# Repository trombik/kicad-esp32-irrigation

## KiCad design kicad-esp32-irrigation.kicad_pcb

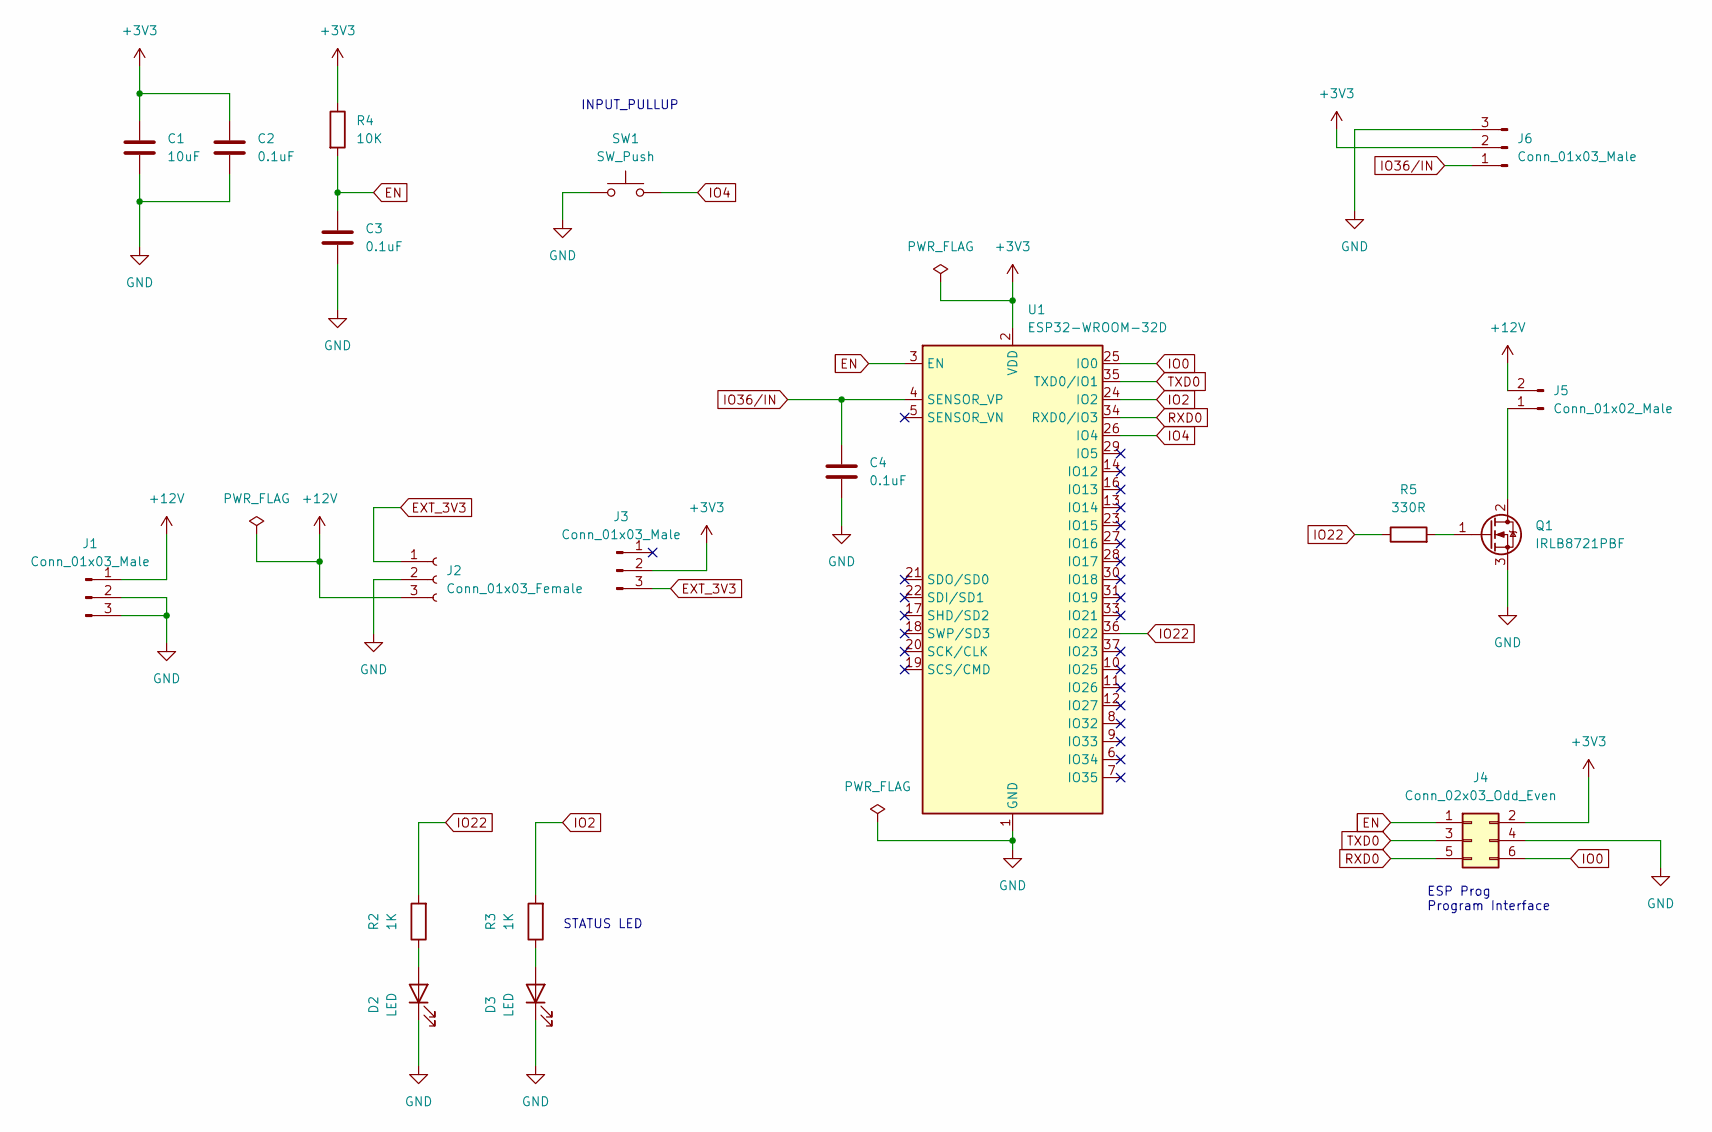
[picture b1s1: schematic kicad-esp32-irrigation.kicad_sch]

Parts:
C1: 10uF; C_Disc_D4.7mm_W2.5mm_P5.00mm
C2, C3, C4: 0.1uF; C_Disc_D4.7mm_W2.5mm_P5.00mm
D2, D3: LED; LED_D3.0mm
J1, J3: Conn_01x03_Male; PinHeader_1x03_P2.54mm_Vertical
J2: Conn_01x03_Female; PinSocket_1x03_P2.54mm_Vertical
J4: Conn_02x03_Odd_Even; IDC-Header_2x03_P2.54mm_Vertical
J5: Conn_01x02_Male; JST_XH_B2B-XH-A_1x02_P2.50mm_Vertical
J6: Conn_01x03_Male
Q1: IRLB8721PBF; TO-220-3_Vertical
R2, R3: 1K; R_Axial_DIN0204_L3.6mm_D1.6mm_P5.08mm_Horizontal
R4: 10K; R_Axial_DIN0204_L3.6mm_D1.6mm_P5.08mm_Horizontal
R5: 330R; R_Axial_DIN0204_L3.6mm_D1.6mm_P5.08mm_Horizontal
SW1: SW_Push; SW_PUSH_6mm_H5mm
U1: ESP32-WROOM-32D; ESP32-WROOM-32

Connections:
+3V3: C1.1, C2.1, J3.2, J4.2, J6.2, R4.1, U1.2 (VDD)
+12V: J1.1, J2.3, J5.2
EN: C3.1, J4.1, R4.2, U1.3 (EN)
EXT_3V3: J2.1, J3.3
GND: C1.2, C2.2, C3.2, C4.2, D2.1 (K), D3.1 (K), J1.2, J1.3, J2.2, J4.4, J6.3, Q1.3 (S), SW1.1, U1.1 (GND), U1.15 (GND), U1.38 (GND), U1.39 (GND)
IO0: J4.6, U1.25 (IO0)
IO2: R3.2, U1.24 (IO2)
IO4: SW1.2, U1.26 (IO4)
IO22: R2.2, R5.1, U1.36 (IO22)
IO36/IN: C4.1, J6.1, U1.4 (SENSOR_VP)
unnamed: D2.2 (A), R2.1
unnamed: D3.2 (A), R3.1
unnamed: Q1.1 (G), R5.2
unnamed: J5.1, Q1.2 (D)
RXD0: J4.5, U1.34 (RXD0/IO3)
TXD0: J4.3, U1.35 (TXD0/IO1)

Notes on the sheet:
ESP Prog Program Interface
STATUS LED
INPUT_PULLUP

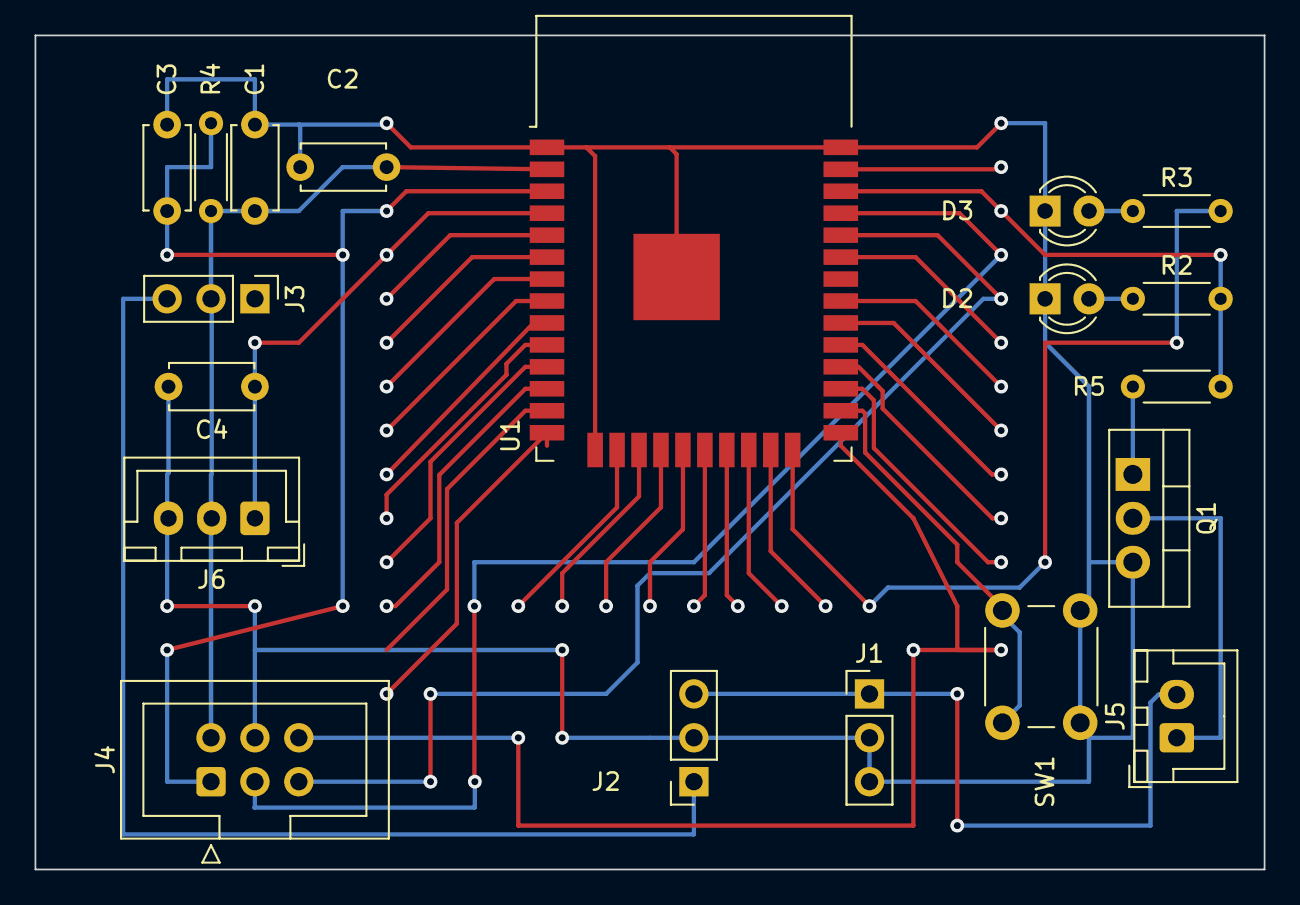
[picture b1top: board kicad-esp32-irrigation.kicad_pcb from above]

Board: 2 copper layers, 71.1 x 48.3 mm, 19 parts (0 on the bottom side), 16 nets.

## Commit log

2022-07-08 initial import
